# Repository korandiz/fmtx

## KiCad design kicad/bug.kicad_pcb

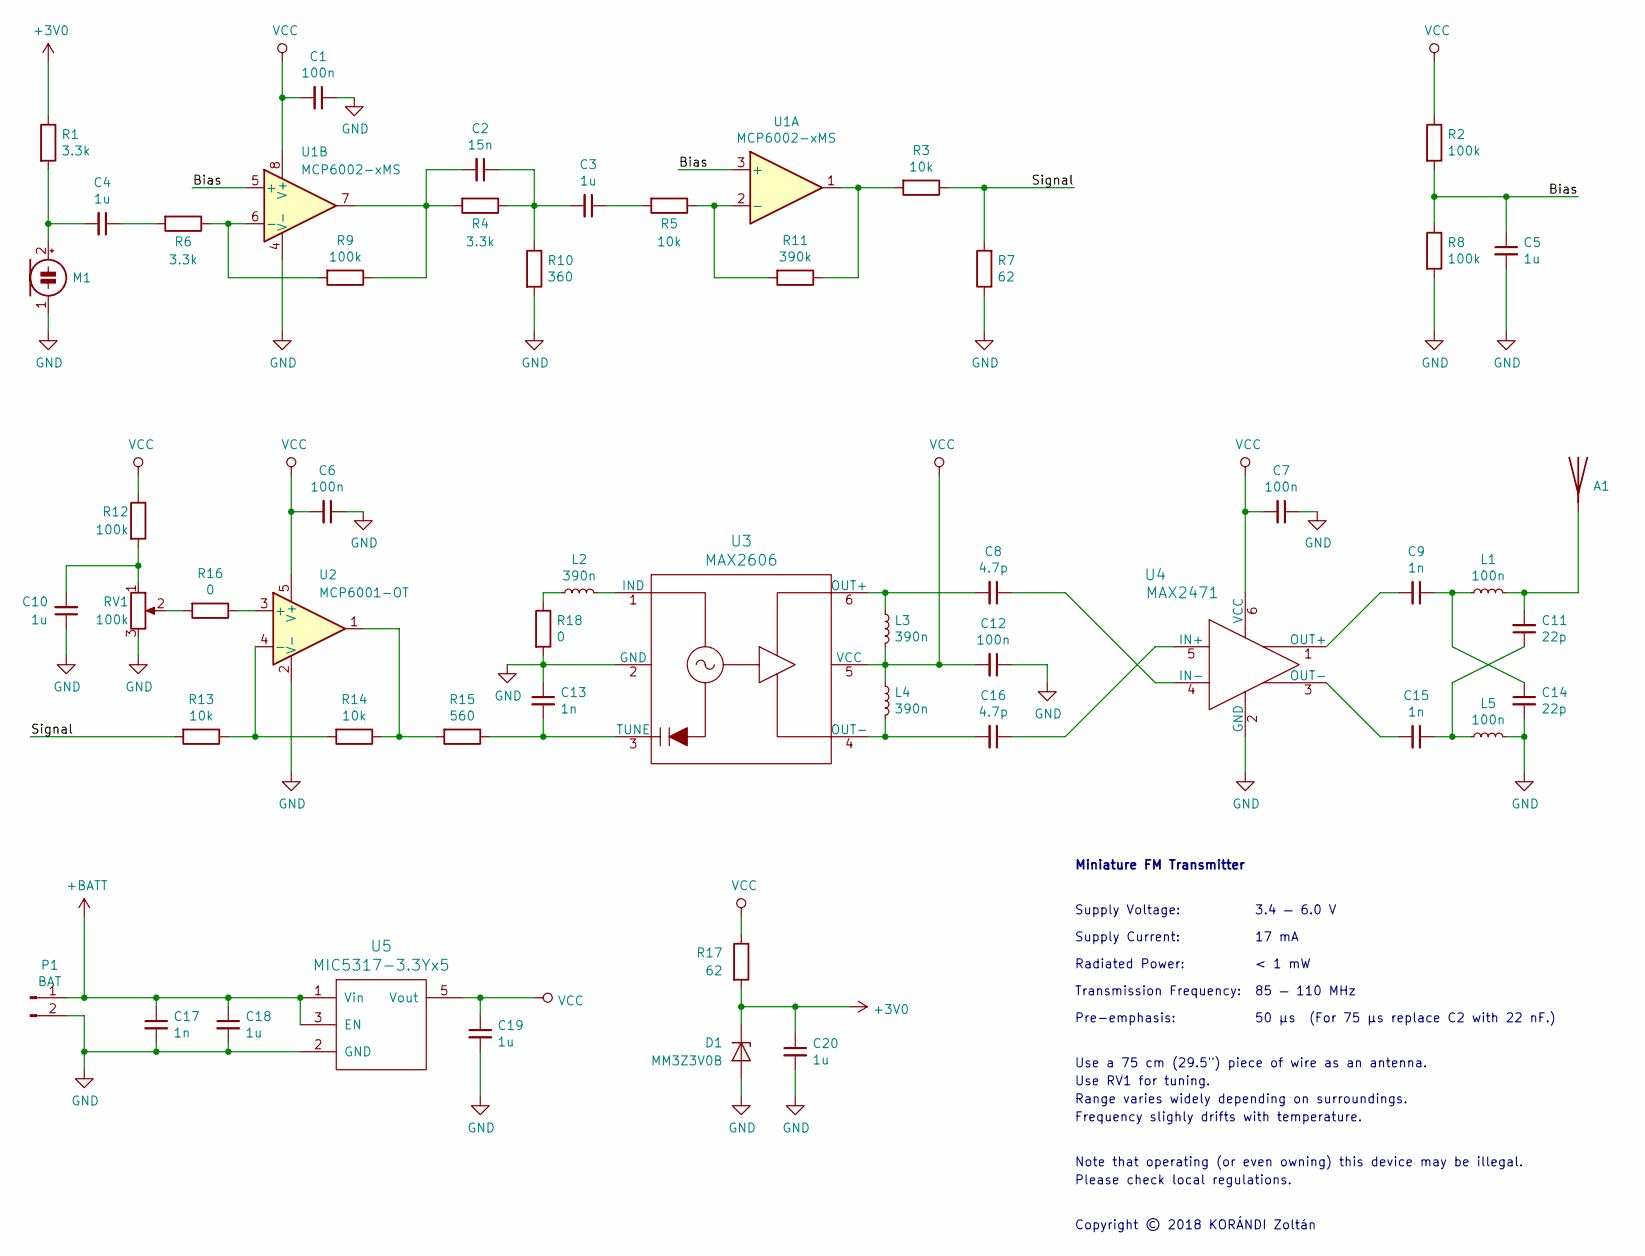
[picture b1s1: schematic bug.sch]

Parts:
A1: Antenna_Pad
C1, C6, C7, C12: 100n; C_0805_2012Metric
C2: 15n; C_0805_2012Metric
C3, C4, C5, C10, C18, C19, C20: 1u; C_0805_2012Metric
C8, C16: 4.7p; C_0805_2012Metric
C9, C13, C15, C17: 1n; C_0805_2012Metric
C11, C14: 22p; C_0805_2012Metric
D1: MM3Z3V0B; D_SOD-323F
L1, L5: 100n; L_0805_2012Metric
L2, L3, L4: 390n; L_0805_2012Metric
M1: LD-MC-0905P
P1: BAT; PinHeader_1x02_P2.54mm_Horizontal
R1, R4, R6: 3.3k; R_0805_2012Metric
R2, R8, R9, R12: 100k; R_0805_2012Metric
R3, R5, R13, R14: 10k; R_0805_2012Metric
R7, R17: 62; R_0805_2012Metric
R10: 360; R_0805_2012Metric
R11: 390k; R_0805_2012Metric
R15: 560; R_0805_2012Metric
R16, R18: 0; R_0805_2012Metric
RV1: 100k; 35W
U1: MCP6002-xMS; MSOP-8_3x3mm_P0.65mm
U2: MCP6001-OT; SOT-23-5
U3: MAX2606; SOT-23-6
U4: MAX2471; SOT-23-6
U5: MIC5317-3.3Yx5; SOT-23-5

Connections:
+3V0: C20.1, D1.1 (K), R1.1, R17.2
+BATT: C17.1, C18.1, P1.1, U5.1 (Vin), U5.3 (EN)
/Bias: C5.1, R2.2, R8.1, U1.3 (+), U1.5 (+)
/Signal: R3.1, R7.2, R13.2
GND: C1.1, C5.2, C6.1, C7.1, C10.1, C12.1, C13.1, C14.2, C17.2, C18.2, C19.2, C20.2, D1.2 (A), L5.2, M1.1 (-), P1.2, R7.1, R8.2, R10.2, R18.2, RV1.3, U1.4 (V-), U2.2 (V-), U3.2 (GND), U4.2 (GND), U5.2 (GND)
unnamed: A1.1, C11.2, L1.2
unnamed: C2.1, C3.2, R4.1, R10.1
unnamed: C2.2, R4.2, R9.1, U1.7
unnamed: C3.1, R5.2
unnamed: C4.1, R6.2
unnamed: C4.2, M1.2 (+), R1.2
unnamed: C8.1, U4.4 (IN-)
unnamed: C8.2, L3.1, U3.6 (OUT+)
unnamed: C9.2, U4.1 (OUT+)
unnamed: C10.2, R12.2, RV1.1
unnamed: C11.1, C15.1, L5.1
unnamed: C13.2, R15.1, U3.3 (TUNE)
unnamed: C9.1, C14.1, L1.1
unnamed: C15.2, U4.3 (OUT-)
unnamed: C16.1, U4.5 (IN+)
unnamed: C16.2, L4.2, U3.4 (OUT-)
unnamed: L2.1, R18.1
unnamed: L2.2, U3.1 (IND)
unnamed: R6.1, R9.2, U1.6 (-)
unnamed: R3.2, R11.1, U1.1
unnamed: R5.1, R11.2, U1.2 (-)
unnamed: R13.1, R14.2, U2.4 (-)
unnamed: R14.1, R15.2, U2.1
unnamed: R16.1, U2.3 (+)
unnamed: R16.2, RV1.2
VCC: C1.2, C6.2, C7.2, C12.2, C19.1, L3.2, L4.1, R2.1, R12.1, R17.1, U1.8 (V+), U2.5 (V+), U3.5 (VCC), U4.6 (VCC), U5.5 (Vout)

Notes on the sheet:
Supply Voltage:
Supply Current:
Radiated Power:
Transmission Frequency:
85 — 110 MHz
3.4 — 6.0 V
17 mA
< 1 mW
Range varies widely depending on surroundings.
Frequency slighly drifts with temperature.
Use a 75 cm (29.5") piece of wire as an antenna.
Miniature FM Transmitter
Use RV1 for tuning.
50 μs
Pre-emphasis:
Note that operating (or even owning) this device may be illegal.
Please check local regulations.
Copyright © 2018 KORÁNDI Zoltán
(For 75 μs replace C2 with 22 nF.)

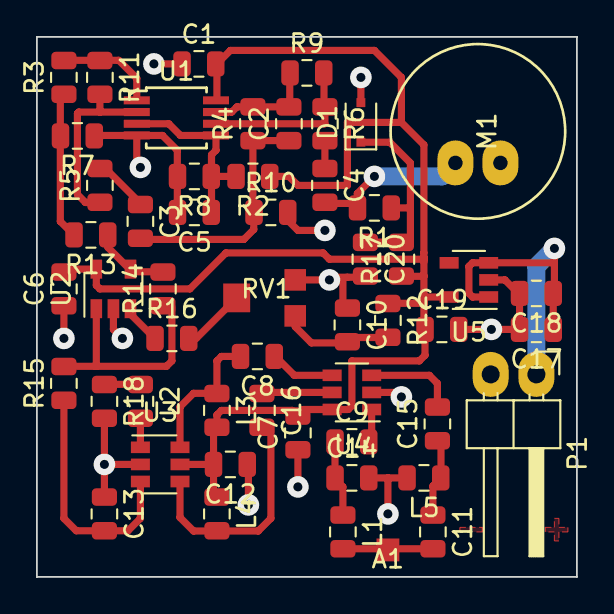
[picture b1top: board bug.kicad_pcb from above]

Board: 2 copper layers, 30.0 x 30.0 mm, 53 parts (0 on the bottom side), 31 nets.
